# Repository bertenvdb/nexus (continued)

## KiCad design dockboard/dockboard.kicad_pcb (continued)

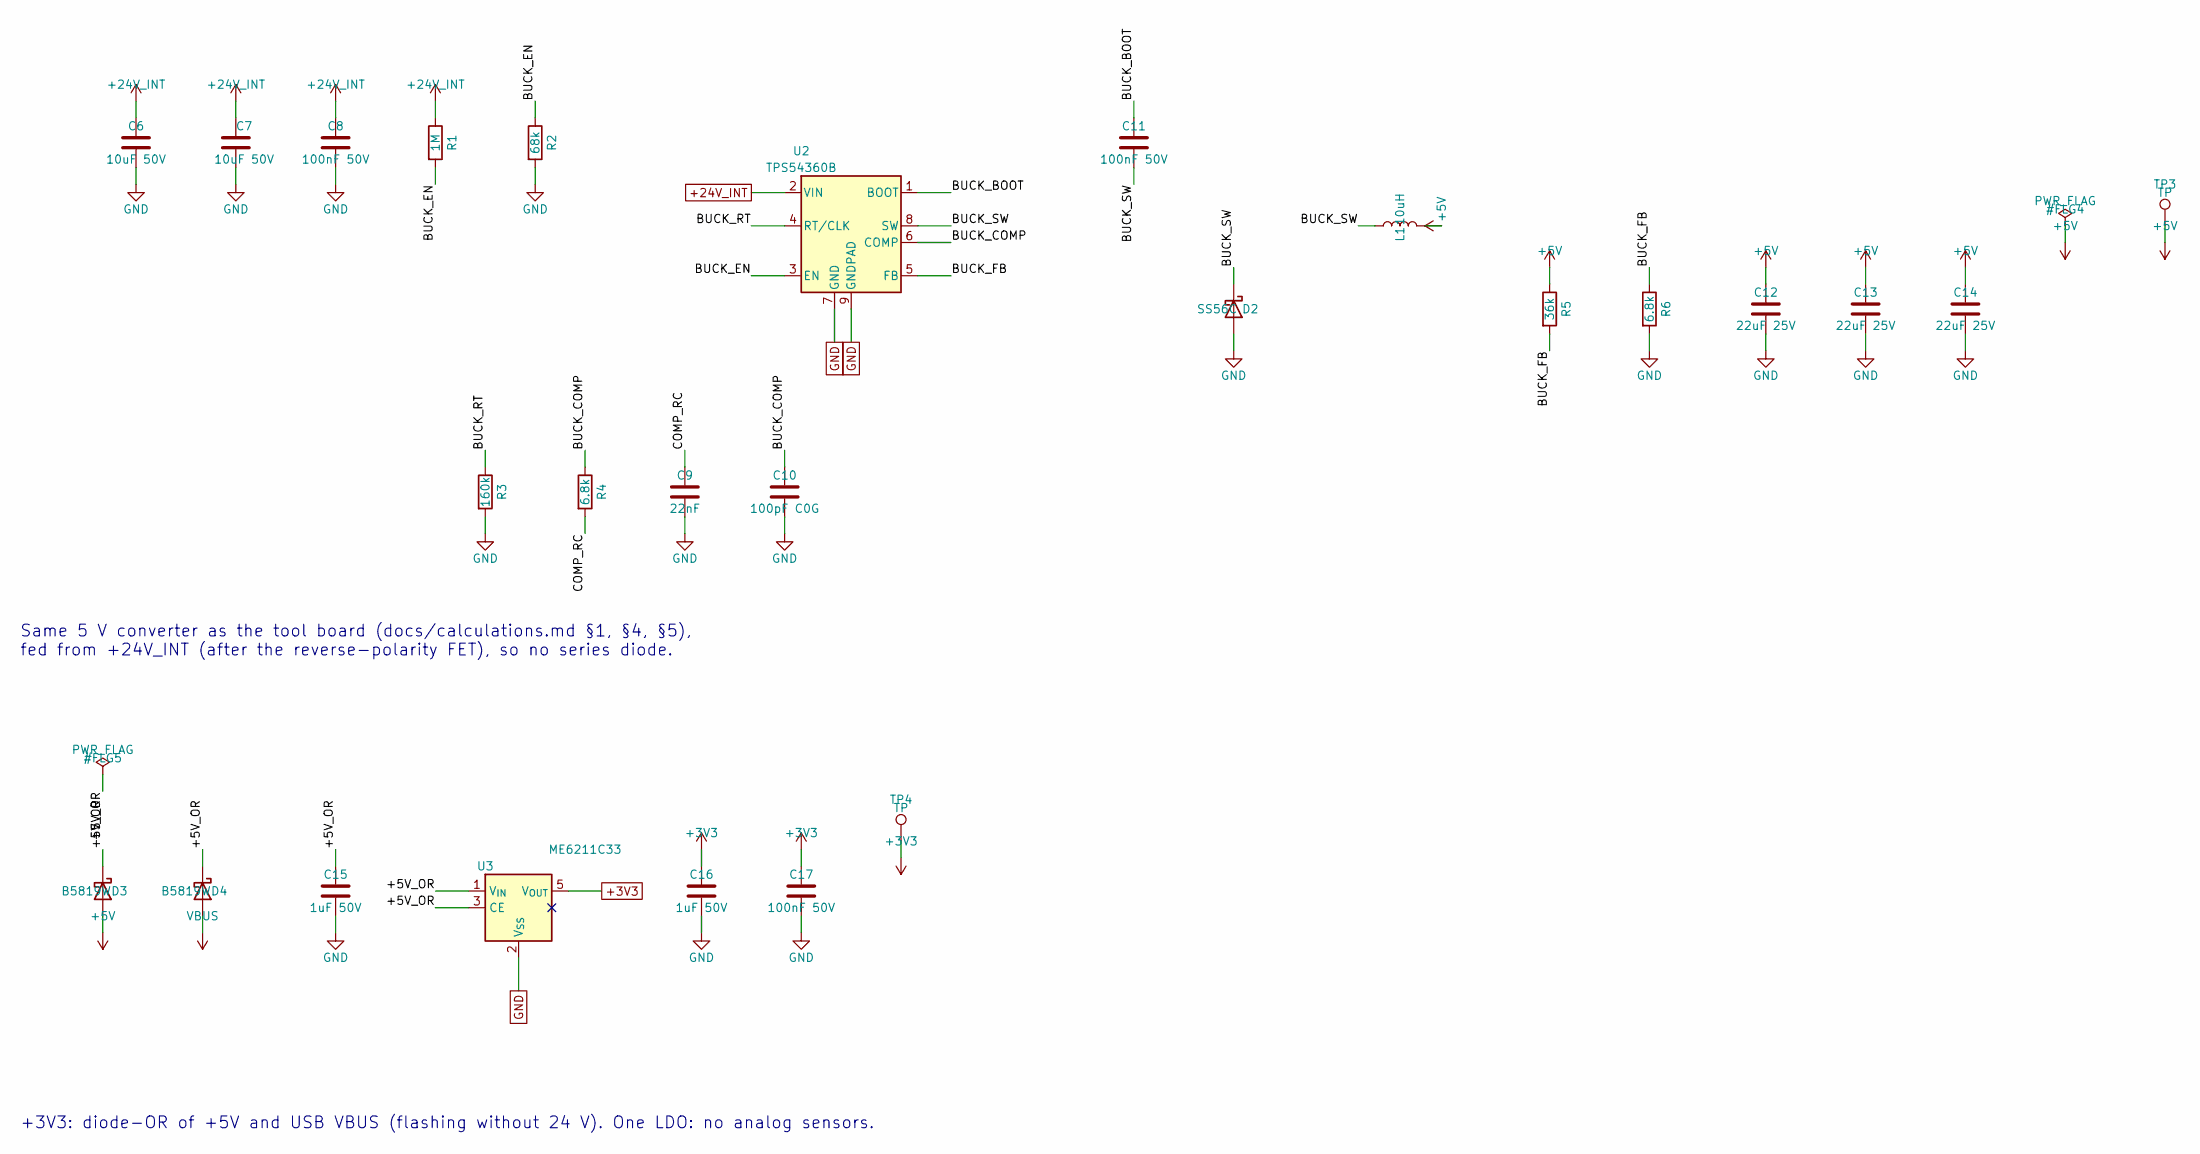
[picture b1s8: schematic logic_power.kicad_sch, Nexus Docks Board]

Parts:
C6, C7: 10uF 50V; C_1206_3216Metric; MPN CL31A106KBHNNNE; LCSC C13585
C8, C11, C17: 100nF 50V; C_0603_1608Metric; MPN CC0603KRX7R9BB104; LCSC C14663
C9: 22nF; C_0603_1608Metric; MPN CL10B223KB8NNNC; LCSC C21122
C10: 100pF C0G; C_0603_1608Metric; MPN CL10C101JB8NNNC; LCSC C14858
C12, C13, C14: 22uF 25V; C_1206_3216Metric; MPN CL31A226KAHNNNE; LCSC C12891
C15, C16: 1uF 50V; C_0603_1608Metric; MPN CL10A105KB8NNNC; LCSC C15849
D2: SS56C; D_SMC; MPN SS56C; LCSC C24138
D3, D4: B5819W; D_SOD-123; MPN B5819W SL; LCSC C8598
L1: 10uH; IND-SMD_L7.1-W6.6; MPN MWSA0603S-100MT; LCSC C132141
R1: 1M; R_0603_1608Metric; MPN 0603WAF1004T5E; LCSC C22935
R2: 68k; R_0603_1608Metric; MPN 0603WAF6802T5E; LCSC C23231
R3: 160k; R_0603_1608Metric; MPN 0603WAF1603T5E; LCSC C22813
R4, R6: 6.8k; R_0603_1608Metric; MPN 0603WAF6801T5E; LCSC C23212
R5: 36k; R_0603_1608Metric; MPN 0603WAF3602T5E; LCSC C23147
TP3, TP4: TP; TestPoint_Pad_D1.0mm
U2: TPS54360B; TI_SO-PowerPAD-8_ThermalVias; MPN TPS54360BDDAR; LCSC C524806
U3: ME6211C33; SOT-23-5; MPN ME6211C33M5G-N; LCSC C82942

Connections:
+3V3: C16.1, C17.1, TP4.1, U3.5 (V_{OUT}); also elsewhere on the board
+5V: C12.1, C13.1, C14.1, D3.2 (A), L1.2, R5.1, TP3.1; also elsewhere on the board
+24V_INT: C6.1, C7.1, C8.1, R1.1, U2.2 (VIN); also elsewhere on the board
/logic_power/+5V_OR: C15.1, D3.1 (K), D4.1 (K), U3.1 (V_{IN}), U3.3 (CE)
/logic_power/BUCK_BOOT: C11.1, U2.1 (BOOT)
/logic_power/BUCK_COMP: C10.1, R4.1, U2.6 (COMP)
/logic_power/BUCK_EN: R1.2, R2.1, U2.3 (EN)
/logic_power/BUCK_FB: R5.2, R6.1, U2.5 (FB)
/logic_power/BUCK_RT: R3.1, U2.4 (RT/CLK)
/logic_power/BUCK_SW: C11.2, D2.1 (K), L1.1, U2.8 (SW)
/logic_power/COMP_RC: C9.1, R4.2
GND: C6.2, C7.2, C8.2, C9.2, C10.2, C12.2, C13.2, C14.2, C15.2, C16.2, C17.2, D2.2 (A), R2.2, R3.2, R6.2, U2.7 (GND), U2.9 (GNDPAD), U3.2 (V_{SS}); also elsewhere on the board
VBUS: D4.2 (A); also elsewhere on the board

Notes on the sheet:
Same 5 V converter as the tool board (docs/calculations.md §1, §4, §5), fed from +24V_INT (after the reverse-polarity FET), so no series diode.
+3V3: diode-OR of +5V and USB VBUS (flashing without 24 V). One LDO: no analog sensors.

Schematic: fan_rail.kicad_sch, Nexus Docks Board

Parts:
C18, C19, C28: 10uF 50V; C_1206_3216Metric; MPN CL31A106KBHNNNE; LCSC C13585
C20, C23: 100nF 50V; C_0603_1608Metric; MPN CC0603KRX7R9BB104; LCSC C14663
C21: 8.2nF; C_0603_1608Metric; MPN 0603B822K500NT; LCSC C1322360
C22: 47pF C0G; C_0603_1608Metric; MPN CL10C470JB8NNNC; LCSC C1671
C24, C25, C26, C27: 22uF 25V; C_1206_3216Metric; MPN CL31A226KAHNNNE; LCSC C12891
D5: SS56C; D_SMC; MPN SS56C; LCSC C24138
JP1: 5V (cut = 12V); SolderJumper-2_P1.3mm_Bridged_RoundedPad1.0x1.5mm
JP2: FAN RAIL 24V|BUCK; SolderJumper-3_P1.3mm_Open_RoundedPad1.0x1.5mm
L2: 10uH; IND-SMD_L7.1-W6.6; MPN MWSA0603S-100MT; LCSC C132141
R7: 1M; R_0603_1608Metric; MPN 0603WAF1004T5E; LCSC C22935
R8, R11: 68k; R_0603_1608Metric; MPN 0603WAF6802T5E; LCSC C23231
R9: 160k; R_0603_1608Metric; MPN 0603WAF1603T5E; LCSC C22813
R10: 12k; R_0603_1608Metric; MPN 0603WAF1202T5E; LCSC C22790
R12: 39k; R_0603_1608Metric; MPN 0603WAF3902T5E; LCSC C23153
R13: 7.5k; R_0603_1608Metric; MPN 0603WAF7501T5E; LCSC C23234
TP5: TP; TestPoint_Pad_D1.0mm
U4: TPS54360B; TI_SO-PowerPAD-8_ThermalVias; MPN TPS54360BDDAR; LCSC C524806

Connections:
+24V_INT: C18.1, C19.1, C20.1, JP2.1 (A), R7.1, U4.2 (VIN); also elsewhere on the board
/fan_rail/FAN_BUCK: C24.1, C25.1, C26.1, C27.1, JP1.1 (A), JP2.3 (B), L2.2, R11.1
/fan_rail/FBK_BOOT: C23.1, U4.1 (BOOT)
/fan_rail/FBK_COMP: C22.1, R10.1, U4.6 (COMP)
/fan_rail/FBK_EN: R7.2, R8.1, U4.3 (EN)
/fan_rail/FBK_FB: R12.2, R13.1, U4.5 (FB)
/fan_rail/FBK_FBM: JP1.2 (B), R11.2, R12.1
/fan_rail/FBK_RC: C21.1, R10.2
/fan_rail/FBK_RT: R9.1, U4.4 (RT/CLK)
/fan_rail/FBK_SW: C23.2, D5.1 (K), L2.1, U4.8 (SW)
FAN_RAIL: C28.1, JP2.2 (C), TP5.1; also elsewhere on the board
GND: C18.2, C19.2, C20.2, C21.2, C22.2, C24.2, C25.2, C26.2, C27.2, C28.2, D5.2 (A), R8.2, R9.2, R13.2, U4.7 (GND), U4.9 (GNDPAD); also elsewhere on the board

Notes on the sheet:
FAN RAIL jumper is OPEN by default: no fan voltage until a choice is made (FR-D02). Bridge 1-2 = 24 V direct, 2-3 = buck (5 V or 12 V). Silkscreen warning next to the jumper. With 24 V direct the buck runs unloaded (pulse skipping, a few mA).
Buck 2: same converter as the 5 V rail. JP_FVSEL bridged (default) = 0.8 x (1 + 39k/7.5k) = 4.96 V; cut = 0.8 x (1 + 107k/7.5k) = 12.2 V. Compensation 12k + 8.2nF // 47pF (calculations.md §5).

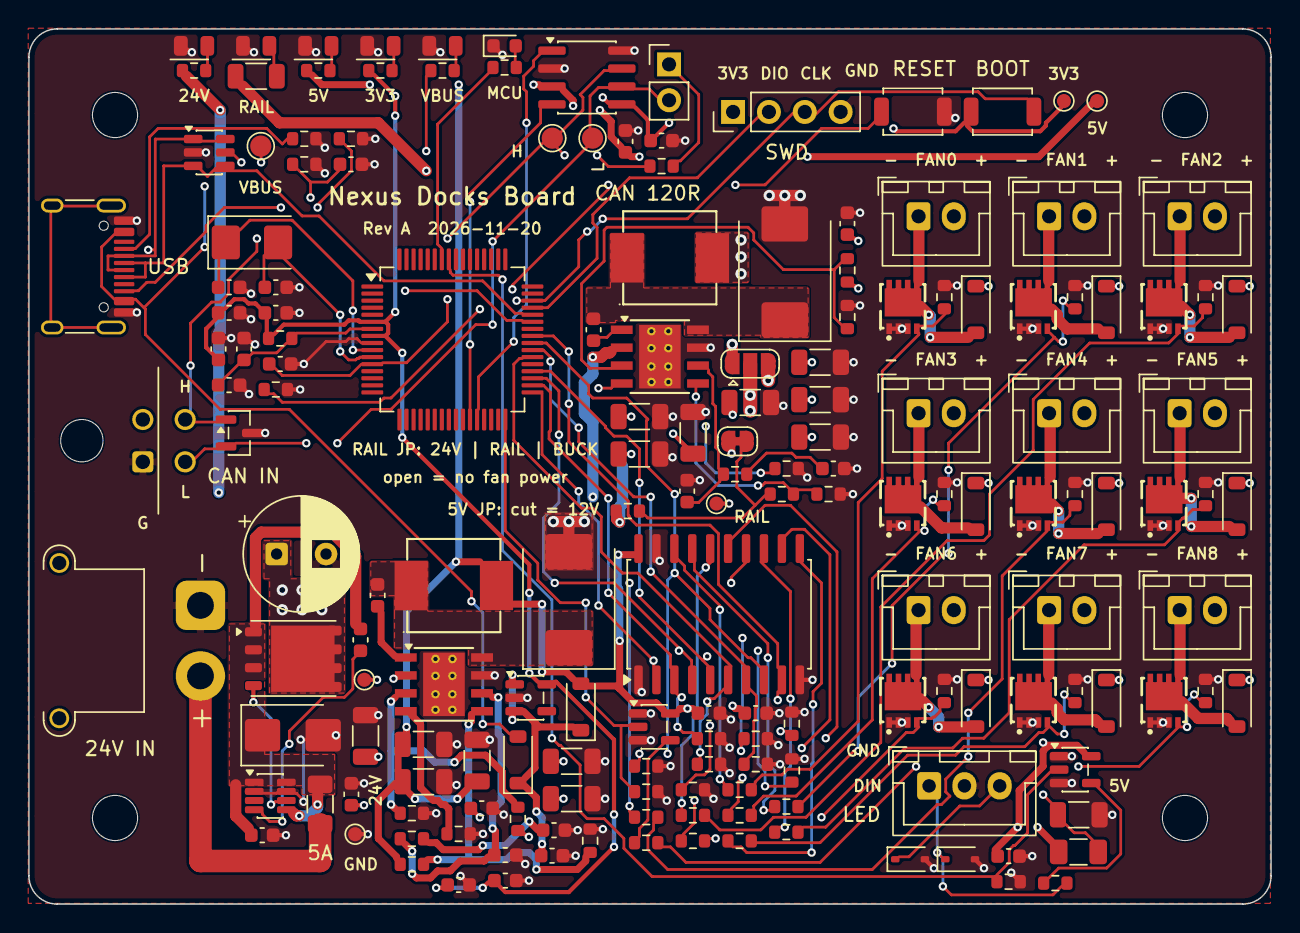
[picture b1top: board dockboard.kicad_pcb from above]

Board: 4 copper layers, 88.0 x 62.0 mm, 176 parts (0 on the bottom side), 90 nets.

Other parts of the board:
H1, H2, H3, H4: M3; MountingHole_3.2mm_M3

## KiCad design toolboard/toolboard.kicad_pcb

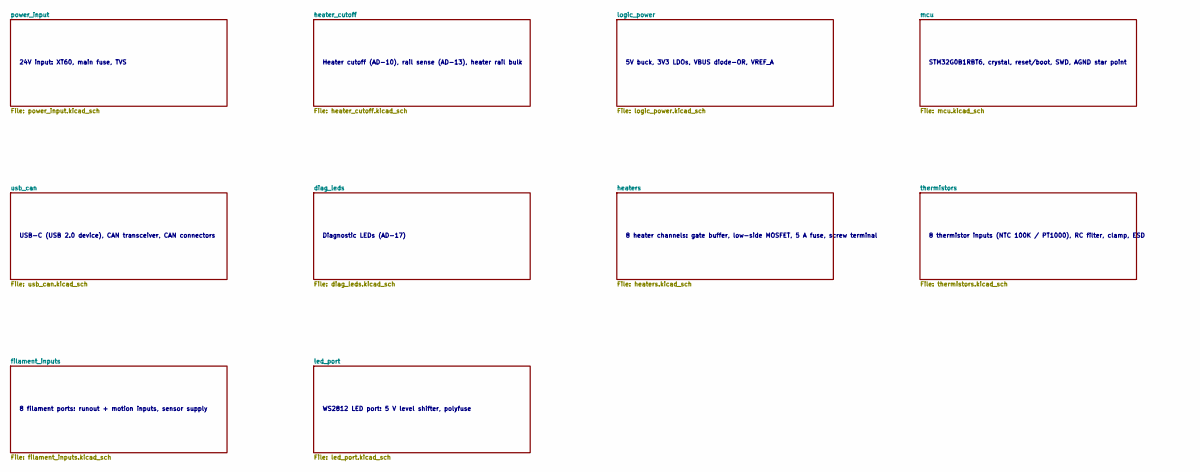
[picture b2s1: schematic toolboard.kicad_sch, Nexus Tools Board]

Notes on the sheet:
8 heater channels: gate buffer, low-side MOSFET, 5 A fuse, screw terminal
Diagnostic LEDs (AD-17)
WS2812 LED port: 5 V level shifter, polyfuse
8 filament ports: runout + motion inputs, sensor supply
5V buck, 3V3 LDOs, VBUS diode-OR, VREF_A
24V input: XT60, main fuse, TVS
STM32G0B1RBT6, crystal, reset/boot, SWD, AGND star point
USB-C (USB 2.0 device), CAN transceiver, CAN connectors
Heater cutoff (AD-10), rail sense (AD-13), heater rail bulk
8 thermistor inputs (NTC 100K / PT1000), RC filter, clamp, ESD

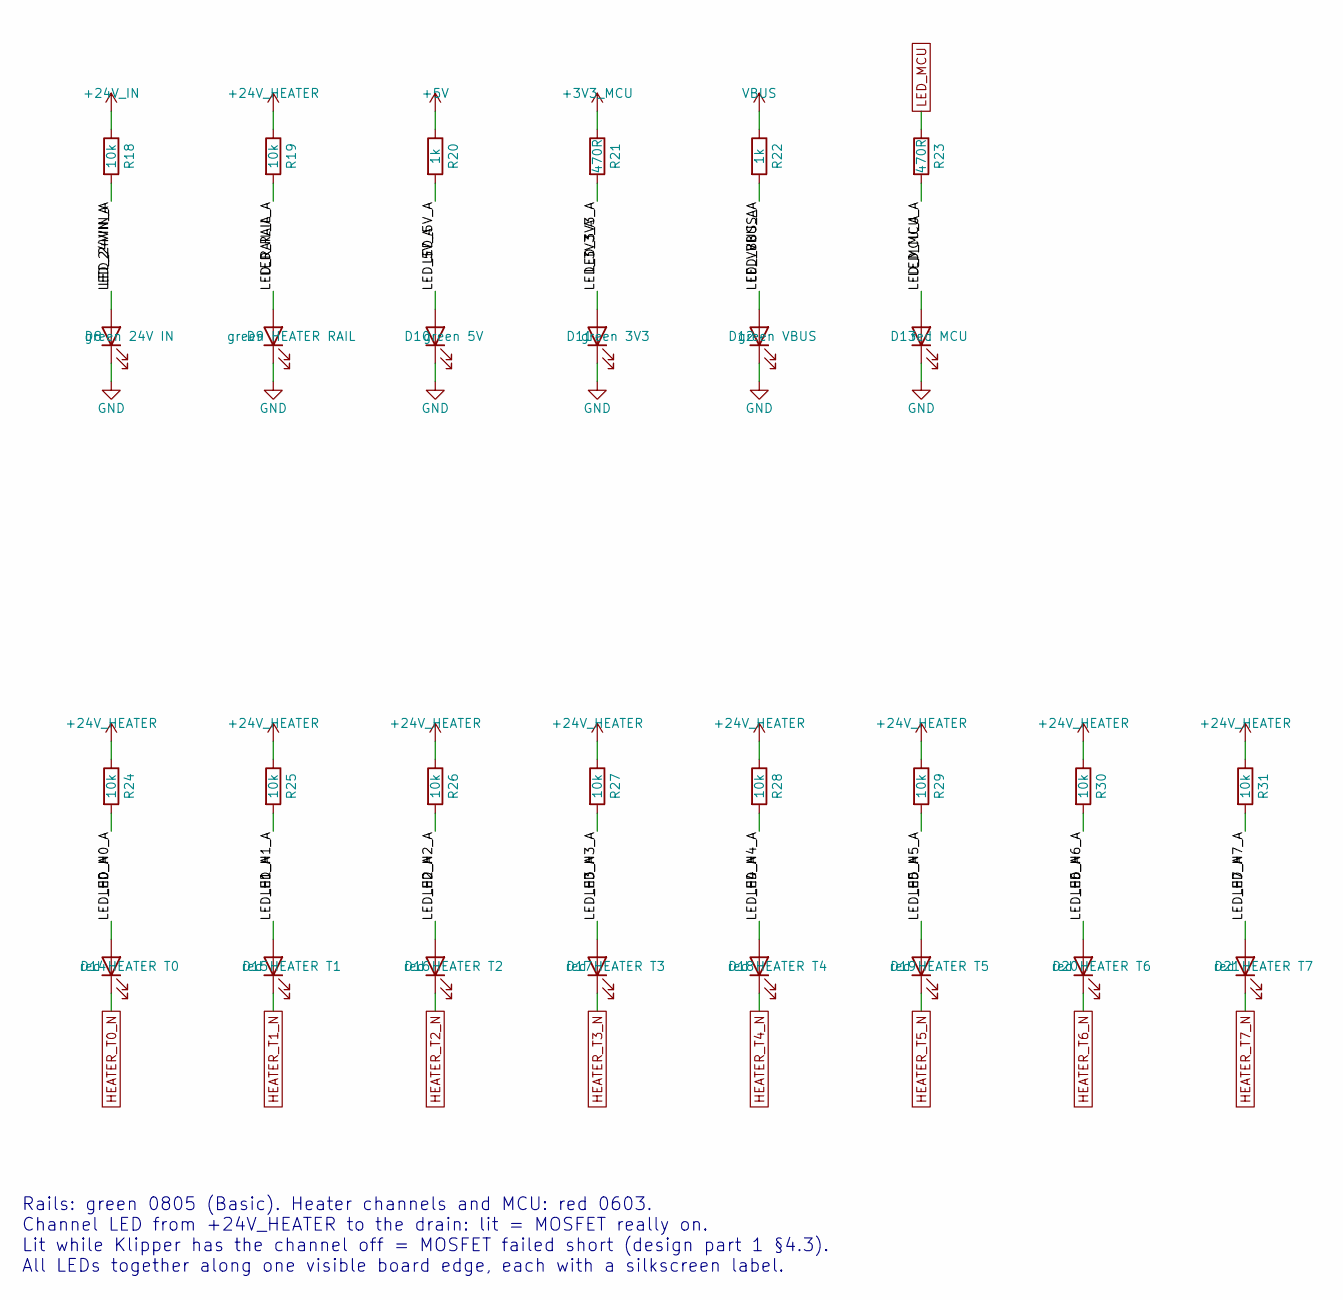
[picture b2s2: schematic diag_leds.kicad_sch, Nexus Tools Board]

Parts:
D8: green 24V IN; LED_0805_2012Metric; MPN KT-0805G; LCSC C2297
D9: green HEATER RAIL; LED_0805_2012Metric; MPN KT-0805G; LCSC C2297
D10: green 5V; LED_0805_2012Metric; MPN KT-0805G; LCSC C2297
D11: green 3V3; LED_0805_2012Metric; MPN KT-0805G; LCSC C2297
D12: green VBUS; LED_0805_2012Metric; MPN KT-0805G; LCSC C2297
D13: red MCU; LED_0603_1608Metric; MPN KT-0603R; LCSC C2286
D14: red HEATER T0; LED_0603_1608Metric; MPN KT-0603R; LCSC C2286
D15: red HEATER T1; LED_0603_1608Metric; MPN KT-0603R; LCSC C2286
D16: red HEATER T2; LED_0603_1608Metric; MPN KT-0603R; LCSC C2286
D17: red HEATER T3; LED_0603_1608Metric; MPN KT-0603R; LCSC C2286
D18: red HEATER T4; LED_0603_1608Metric; MPN KT-0603R; LCSC C2286
D19: red HEATER T5; LED_0603_1608Metric; MPN KT-0603R; LCSC C2286
D20: red HEATER T6; LED_0603_1608Metric; MPN KT-0603R; LCSC C2286
D21: red HEATER T7; LED_0603_1608Metric; MPN KT-0603R; LCSC C2286
R18, R19, R24, R25, R26, R27, R28, R29, R30, R31: 10k; R_0603_1608Metric; MPN 0603WAF1002T5E; LCSC C25804
R20, R22: 1k; R_0603_1608Metric; MPN 0603WAF1001T5E; LCSC C21190
R21, R23: 470R; R_0603_1608Metric; MPN 0603WAF4700T5E; LCSC C23179

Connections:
+3V3_MCU: R21.1; also elsewhere on the board
+5V: R20.1; also elsewhere on the board
+24V_HEATER: R19.1, R24.1, R25.1, R26.1, R27.1, R28.1, R29.1, R30.1, R31.1; also elsewhere on the board
+24V_IN: R18.1; also elsewhere on the board
/diag_leds/LED_3V3_A: D11.2 (A), R21.2
/diag_leds/LED_5V_A: D10.2 (A), R20.2
/diag_leds/LED_24VIN_A: D8.2 (A), R18.2
/diag_leds/LED_H0_A: D14.2 (A), R24.2
/diag_leds/LED_H1_A: D15.2 (A), R25.2
/diag_leds/LED_H2_A: D16.2 (A), R26.2
/diag_leds/LED_H3_A: D17.2 (A), R27.2
/diag_leds/LED_H4_A: D18.2 (A), R28.2
/diag_leds/LED_H5_A: D19.2 (A), R29.2
/diag_leds/LED_H6_A: D20.2 (A), R30.2
/diag_leds/LED_H7_A: D21.2 (A), R31.2
/diag_leds/LED_MCU_A: D13.2 (A), R23.2
/diag_leds/LED_RAIL_A: D9.2 (A), R19.2
/diag_leds/LED_VBUS_A: D12.2 (A), R22.2
GND: D8.1 (K), D9.1 (K), D10.1 (K), D11.1 (K), D12.1 (K), D13.1 (K); also elsewhere on the board
HEATER_T0_N: D14.1 (K); also elsewhere on the board
HEATER_T1_N: D15.1 (K); also elsewhere on the board
HEATER_T2_N: D16.1 (K); also elsewhere on the board
HEATER_T3_N: D17.1 (K); also elsewhere on the board
HEATER_T4_N: D18.1 (K); also elsewhere on the board
HEATER_T5_N: D19.1 (K); also elsewhere on the board
HEATER_T6_N: D20.1 (K); also elsewhere on the board
HEATER_T7_N: D21.1 (K); also elsewhere on the board
LED_MCU: R23.1; also elsewhere on the board
VBUS: R22.1; also elsewhere on the board

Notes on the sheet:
Rails: green 0805 (Basic). Heater channels and MCU: red 0603. Channel LED from +24V_HEATER to the drain: lit = MOSFET really on. Lit while Klipper has the channel off = MOSFET failed short (design part 1 §4.3). All LEDs together along one visible board edge, each with a silkscreen label.

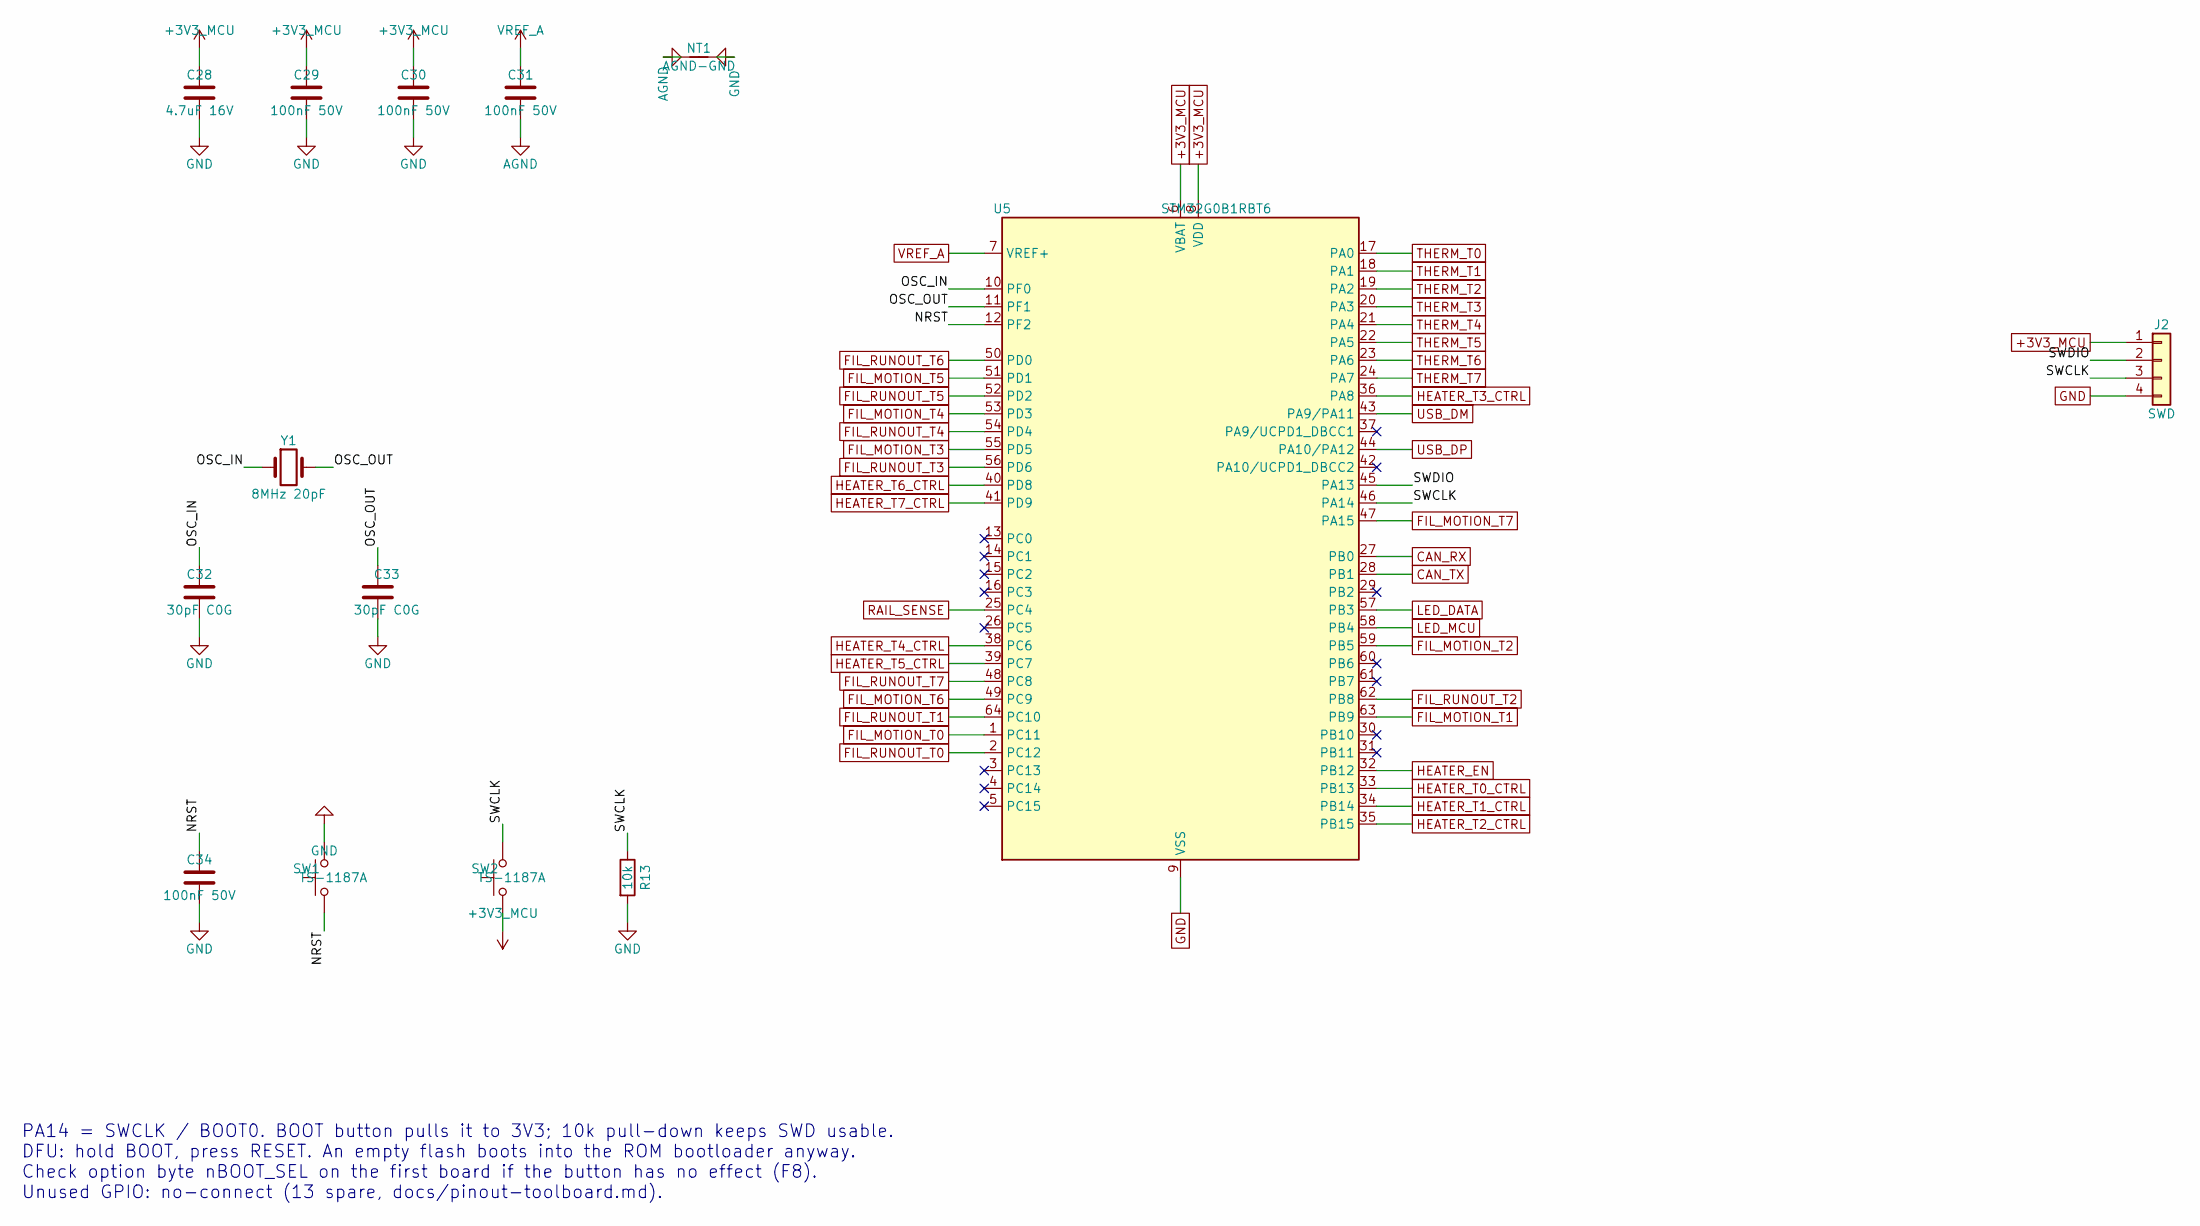
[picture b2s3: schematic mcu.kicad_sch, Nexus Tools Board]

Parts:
C28: 4.7uF 16V; C_0603_1608Metric; MPN CL10A475KO8NNNC; LCSC C19666
C29, C30, C31, C34: 100nF 50V; C_0603_1608Metric; MPN CC0603KRX7R9BB104; LCSC C14663
C32, C33: 30pF C0G; C_0603_1608Metric; MPN 0603CG300J500NT; LCSC C1658
J2: SWD; PinHeader_1x04_P2.54mm_Vertical; MPN HX PZ2.54-1x4P ZZ; LCSC C32713270
NT1: AGND-GND; NetTie-2_SMD_Pad0.5mm
R13: 10k; R_0603_1608Metric; MPN 0603WAF1002T5E; LCSC C25804
SW1, SW2: TS-1187A; SW_Push_1P1T_XKB_TS-1187A; MPN TS-1187A-B-A-B; LCSC C318884
U5: STM32G0B1RBT6; LQFP-64_10x10mm_P0.5mm; MPN STM32G0B1RBT6; LCSC C5143679
Y1: 8MHz 20pF; Crystal_SMD_5032-2Pin_5.0x3.2mm; MPN X50328MSB2GI; LCSC C115962

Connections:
+3V3_MCU: C28.1, C29.1, C30.1, J2.1, SW2.1, U5.6 (VBAT), U5.8 (VDD); also elsewhere on the board
/mcu/NRST: C34.1, SW1.1, U5.12 (PF2)
/mcu/OSC_IN: C32.1, U5.10 (PF0), Y1.1
/mcu/OSC_OUT: C33.1, U5.11 (PF1), Y1.2
/mcu/SWCLK: J2.3, R13.1, SW2.2, U5.46 (PA14)
/mcu/SWDIO: J2.2, U5.45 (PA13)
AGND: C31.2, NT1.1; also elsewhere on the board
CAN_RX: U5.27 (PB0); also elsewhere on the board
CAN_TX: U5.28 (PB1); also elsewhere on the board
FIL_MOTION_T0: U5.1 (PC11); also elsewhere on the board
FIL_MOTION_T1: U5.63 (PB9); also elsewhere on the board
FIL_MOTION_T2: U5.59 (PB5); also elsewhere on the board
FIL_MOTION_T3: U5.55 (PD5); also elsewhere on the board
FIL_MOTION_T4: U5.53 (PD3); also elsewhere on the board
FIL_MOTION_T5: U5.51 (PD1); also elsewhere on the board
FIL_MOTION_T6: U5.49 (PC9); also elsewhere on the board
FIL_MOTION_T7: U5.47 (PA15); also elsewhere on the board
FIL_RUNOUT_T0: U5.2 (PC12); also elsewhere on the board
FIL_RUNOUT_T1: U5.64 (PC10); also elsewhere on the board
FIL_RUNOUT_T2: U5.62 (PB8); also elsewhere on the board
FIL_RUNOUT_T3: U5.56 (PD6); also elsewhere on the board
FIL_RUNOUT_T4: U5.54 (PD4); also elsewhere on the board
FIL_RUNOUT_T5: U5.52 (PD2); also elsewhere on the board
FIL_RUNOUT_T6: U5.50 (PD0); also elsewhere on the board
FIL_RUNOUT_T7: U5.48 (PC8); also elsewhere on the board
GND: C28.2, C29.2, C30.2, C32.2, C33.2, C34.2, J2.4, NT1.2, R13.2, SW1.2, U5.9 (VSS); also elsewhere on the board
HEATER_EN: U5.32 (PB12); also elsewhere on the board
HEATER_T0_CTRL: U5.33 (PB13); also elsewhere on the board
HEATER_T1_CTRL: U5.34 (PB14); also elsewhere on the board
HEATER_T2_CTRL: U5.35 (PB15); also elsewhere on the board
HEATER_T3_CTRL: U5.36 (PA8); also elsewhere on the board
HEATER_T4_CTRL: U5.38 (PC6); also elsewhere on the board
HEATER_T5_CTRL: U5.39 (PC7); also elsewhere on the board
HEATER_T6_CTRL: U5.40 (PD8); also elsewhere on the board
HEATER_T7_CTRL: U5.41 (PD9); also elsewhere on the board
LED_DATA: U5.57 (PB3); also elsewhere on the board
LED_MCU: U5.58 (PB4); also elsewhere on the board
RAIL_SENSE: U5.25 (PC4); also elsewhere on the board
THERM_T0: U5.17 (PA0); also elsewhere on the board
THERM_T1: U5.18 (PA1); also elsewhere on the board
THERM_T2: U5.19 (PA2); also elsewhere on the board
THERM_T3: U5.20 (PA3); also elsewhere on the board
THERM_T4: U5.21 (PA4); also elsewhere on the board
THERM_T5: U5.22 (PA5); also elsewhere on the board
THERM_T6: U5.23 (PA6); also elsewhere on the board
THERM_T7: U5.24 (PA7); also elsewhere on the board
USB_DM: U5.43 (PA9/PA11); also elsewhere on the board
USB_DP: U5.44 (PA10/PA12); also elsewhere on the board
VREF_A: C31.1, U5.7 (VREF+); also elsewhere on the board

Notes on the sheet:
PA14 = SWCLK / BOOT0. BOOT button pulls it to 3V3; 10k pull-down keeps SWD usable. DFU: hold BOOT, press RESET. An empty flash boots into the ROM bootloader anyway. Check option byte nBOOT_SEL on the first board if the button has no effect (F8). Unused GPIO: no-connect (13 spare, docs/pinout-toolbo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

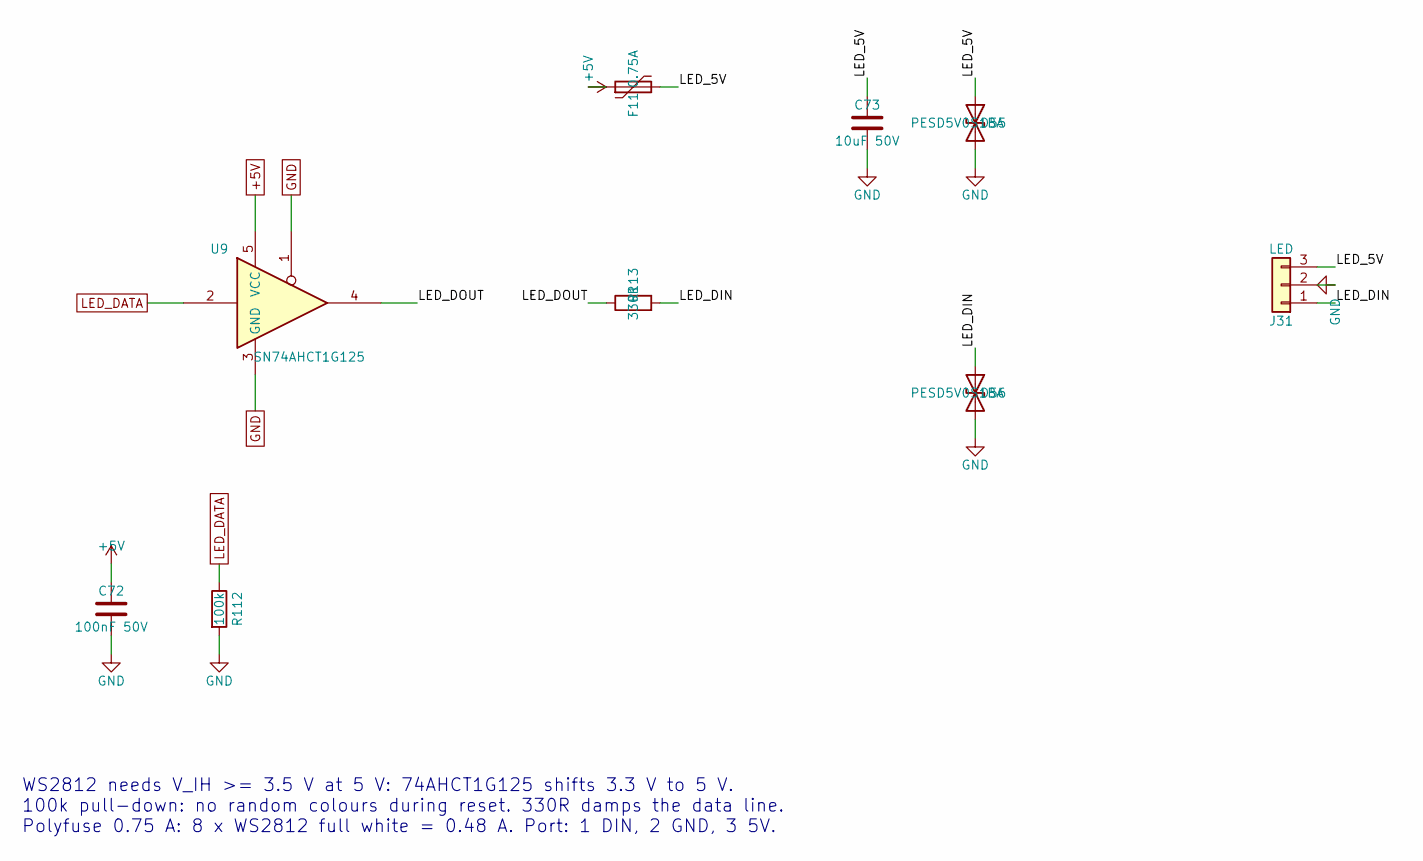
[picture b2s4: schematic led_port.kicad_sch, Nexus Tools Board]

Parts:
C72: 100nF 50V; C_0603_1608Metric; MPN CC0603KRX7R9BB104; LCSC C14663
C73: 10uF 50V; C_1206_3216Metric; MPN CL31A106KBHNNNE; LCSC C13585
D55, D56: PESD5V0S1BA; D_SOD-323; MPN PESD5V0S1BA; LCSC C2827694
F11: 0.75A; Fuse_1206_3216Metric; MPN JK-nSMD075-16; LCSC C409806
J31: LED; JST_XH_B3B-XH-A_1x03_P2.50mm_Vertical; MPN B3B-XH-A(LF)(SN); LCSC C144394
R112: 100k; R_0603_1608Metric; MPN 0603WAF1003T5E; LCSC C25803
R113: 330R; R_0603_1608Metric; MPN 0603WAF3300T5E; LCSC C23138
U9: SN74AHCT1G125; SOT-23-5; MPN SN74AHCT1G125DBVR; LCSC C7484

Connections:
+5V: C72.1, F11.1, U9.5 (VCC); also elsewhere on the board
/led_port/LED_5V: C73.1, D55.1 (A1), F11.2, J31.3
/led_port/LED_DIN: D56.1 (A1), J31.1, R113.2
/led_port/LED_DOUT: R113.1, U9.4
GND: C72.2, C73.2, D55.2 (A2), D56.2 (A2), J31.2, R112.2, U9.1, U9.3 (GND); also elsewhere on the board
LED_DATA: R112.1, U9.2; also elsewhere on the board

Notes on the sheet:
WS2812 needs V_IH >= 3.5 V at 5 V: 74AHCT1G125 shifts 3.3 V to 5 V. 100k pull-down: no random colours during reset. 330R damps the data line. Polyfuse 0.75 A: 8 x WS2812 full white = 0.48 A. Port: 1 DIN, 2 GND, 3 5V.

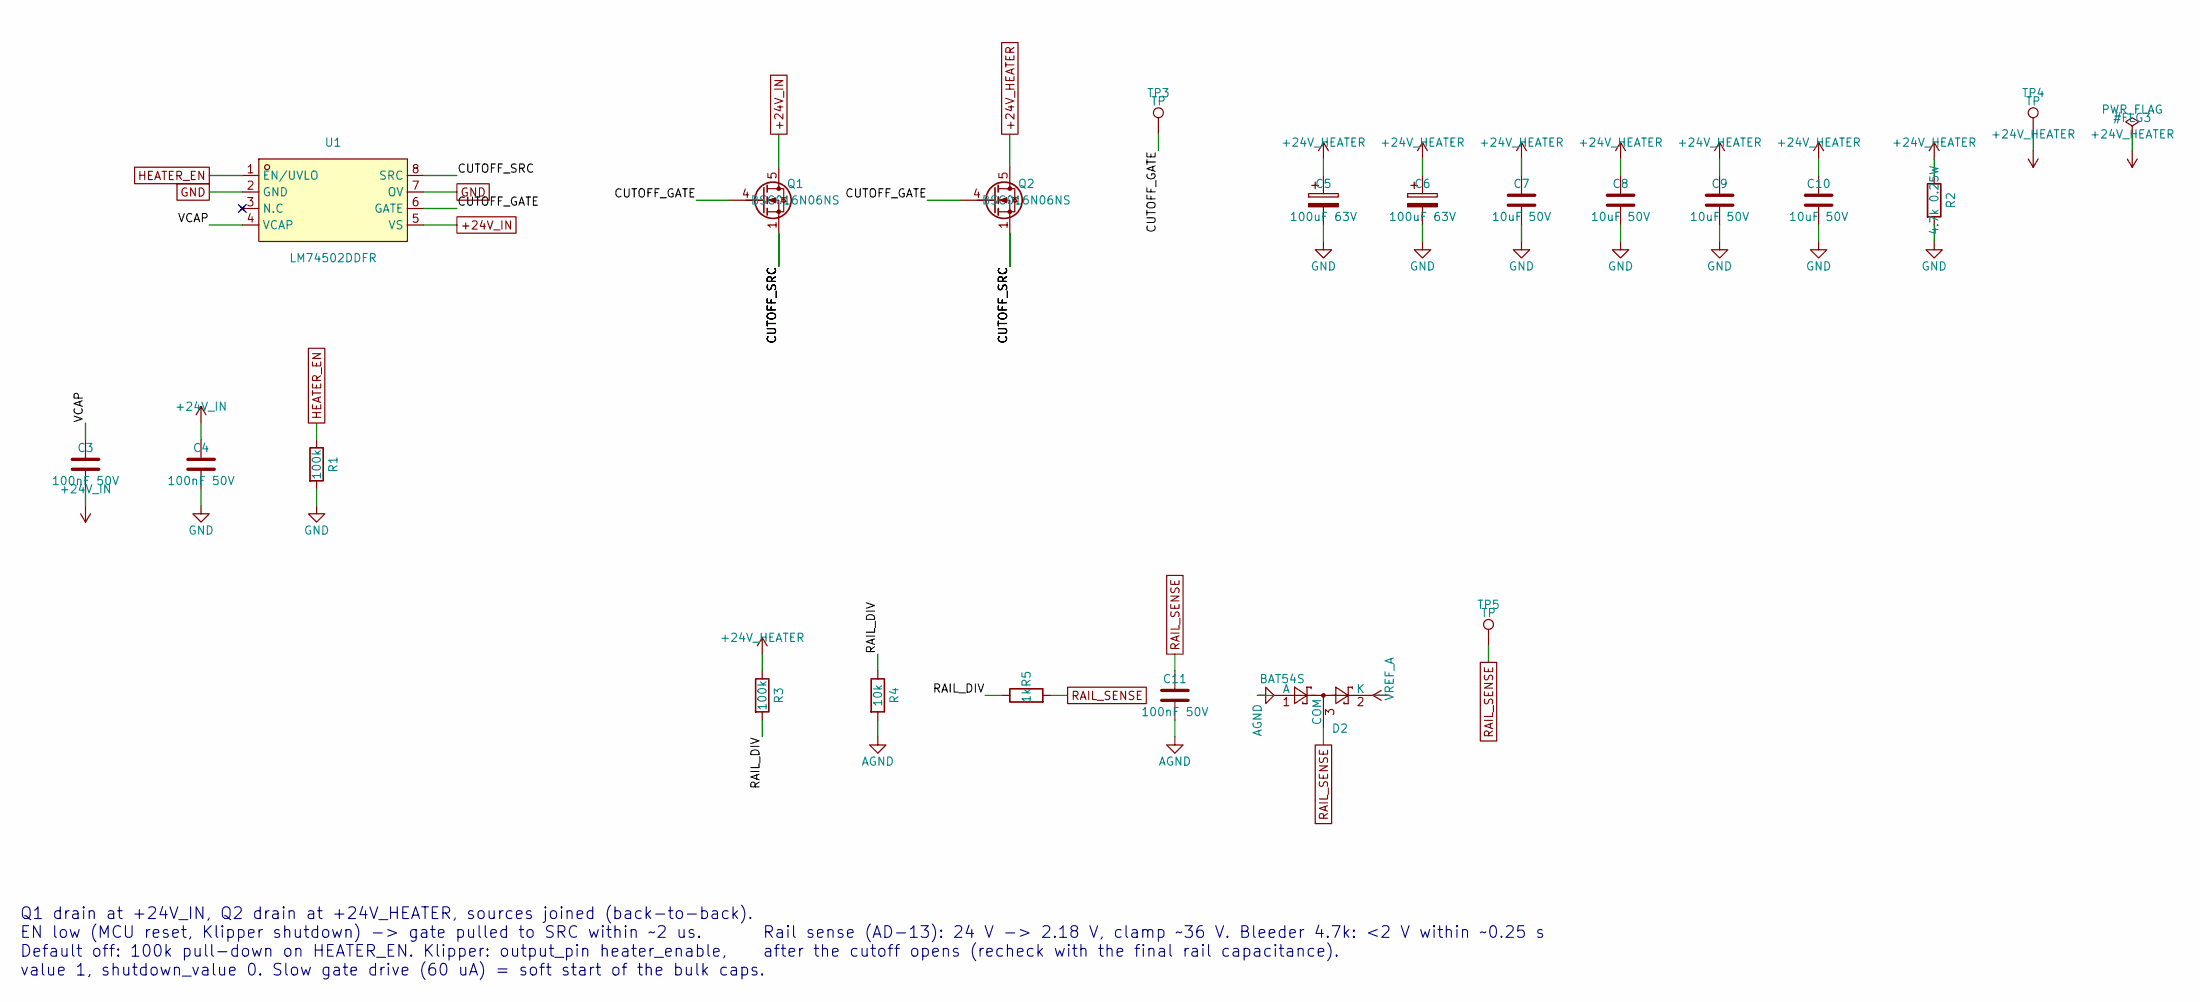
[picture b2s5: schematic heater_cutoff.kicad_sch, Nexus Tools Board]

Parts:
C3, C4, C11: 100nF 50V; C_0603_1608Metric; MPN CC0603KRX7R9BB104; LCSC C14663
C5, C6: 100uF 63V; CP_Radial_D8.0mm_P3.50mm; MPN 63ZLH100MEFC8X16; LCSC C88747
C7, C8, C9, C10: 10uF 50V; C_1206_3216Metric; MPN CL31A106KBHNNNE; LCSC C13585
D2: BAT54S; SOT-23; MPN BAT54S; LCSC C408389
Q1, Q2: BSC016N06NS; Infineon_PG-TDSON-8_6.15x5.15mm; MPN BSC016N06NS; LCSC C454269
R1, R3: 100k; R_0603_1608Metric; MPN 0603WAF1003T5E; LCSC C25803
R2: 4.7k 0.25W; R_1206_3216Metric; MPN 1206W4F4701T5E; LCSC C17936
R4: 10k; R_0603_1608Metric; MPN 0603WAF1002T5E; LCSC C25804
R5: 1k; R_0603_1608Metric; MPN 0603WAF1001T5E; LCSC C21190
TP3, TP4, TP5: TP; TestPoint_Pad_D1.5mm
U1: LM74502DDFR; TSOT-23-8; MPN LM74502DDFR; LCSC C3236215

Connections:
+24V_HEATER: C5.1, C6.1, C7.1, C8.1, C9.1, C10.1, Q2.5 (D), R2.1, R3.1, TP4.1; also elsewhere on the board
+24V_IN: C3.2, C4.1, Q1.5 (D), U1.5 (VS); also elsewhere on the board
/heater_cutoff/CUTOFF_GATE: Q1.4 (G), Q2.4 (G), TP3.1, U1.6 (GATE)
/heater_cutoff/CUTOFF_SRC: Q1.1 (S), Q1.2 (S), Q1.3 (S), Q2.1 (S), Q2.2 (S), Q2.3 (S), U1.8 (SRC)
/heater_cutoff/RAIL_DIV: R3.2, R4.1, R5.1
/heater_cutoff/VCAP: C3.1, U1.4 (VCAP)
AGND: C11.2, D2.1 (A), R4.2; also elsewhere on the board
GND: C4.2, C5.2, C6.2, C7.2, C8.2, C9.2, C10.2, R1.2, R2.2, U1.2 (GND), U1.7 (OV); also elsewhere on the board
HEATER_EN: R1.1, U1.1 (EN/UVLO); also elsewhere on the board
RAIL_SENSE: C11.1, D2.3 (COM), R5.2, TP5.1; also elsewhere on the board
VREF_A: D2.2 (K); also elsewhere on the board

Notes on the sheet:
Rail sense (AD-13): 24 V -> 2.18 V, clamp ~36 V. Bleeder 4.7k: <2 V within ~0.25 s after the cutoff opens (recheck with the final rail capacitance).
Q1 drain at +24V_IN, Q2 drain at +24V_HEATER, sources joined (back-to-back). EN low (MCU reset, Klipper shutdown) -> gate pulled to SRC within ~2 us. Default off: 100k pull-down on HEATER_EN. Klipper: output_pin heater_enable, value 1, shutdown_value 0. Slow gate drive (60 uA) = soft start of the b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
